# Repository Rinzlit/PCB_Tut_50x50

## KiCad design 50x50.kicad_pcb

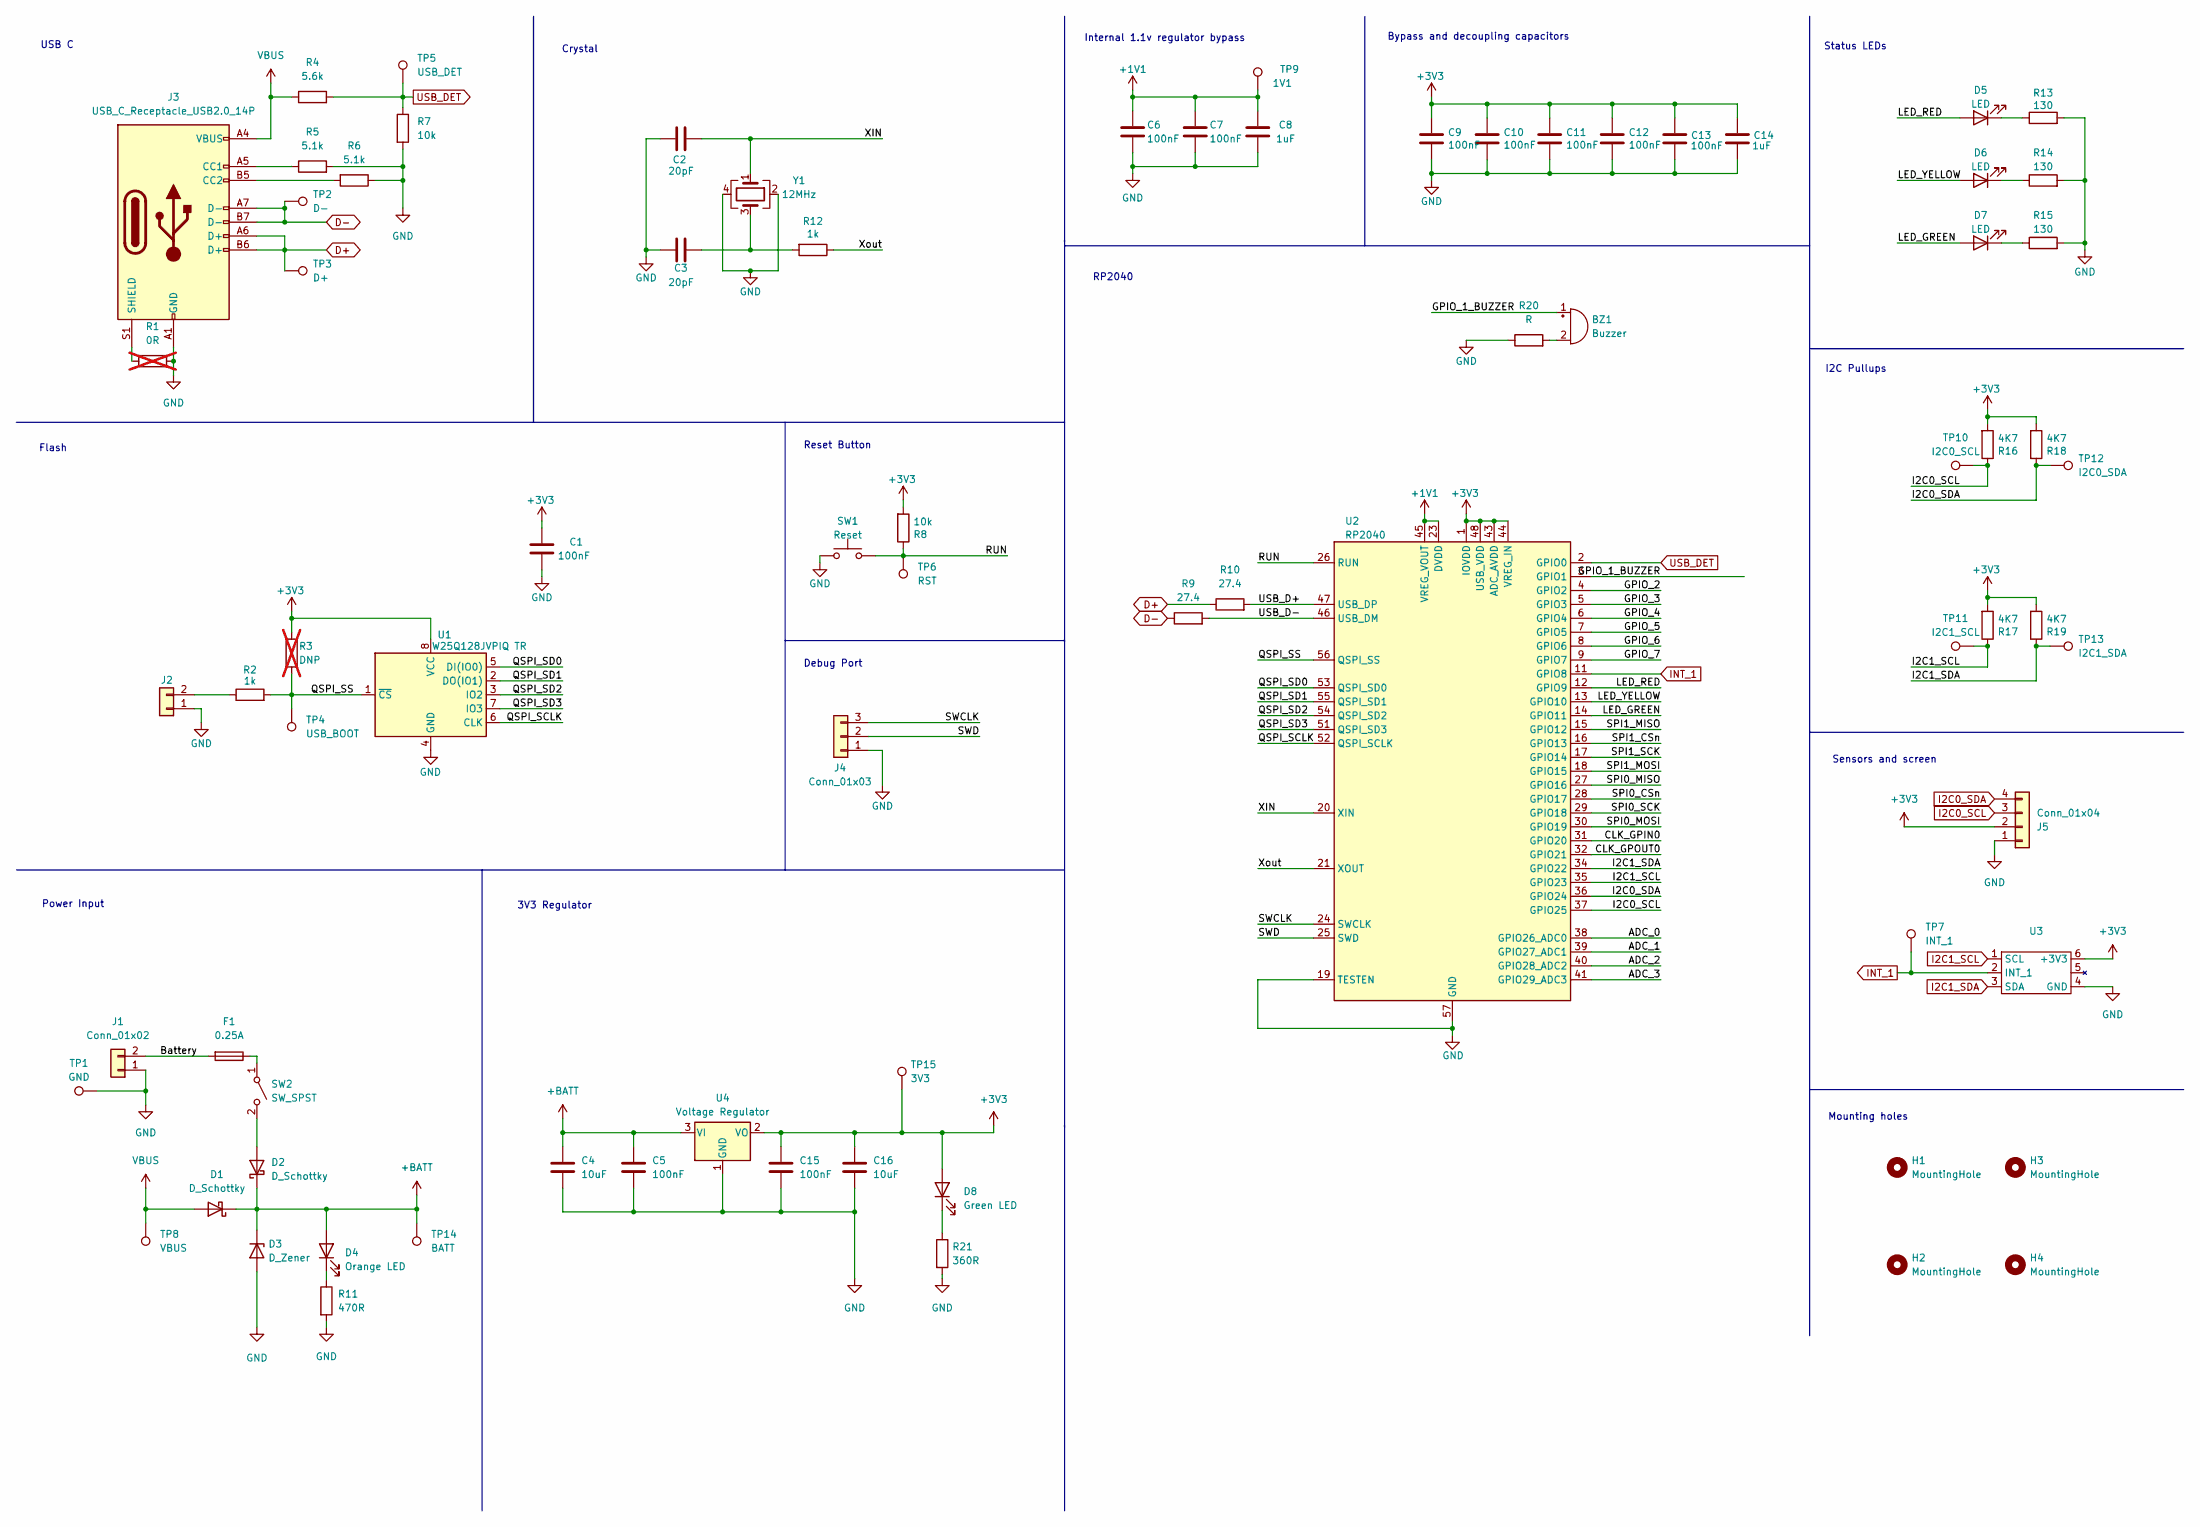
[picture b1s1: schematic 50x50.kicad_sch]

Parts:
BZ1: Buzzer; Buzzer_12x9.5RM7.6
C1, C5, C6, C7, C9, C10, C11, C12, C13, C15: 100nF; C_0805_2012Metric_Pad1.18x1.45mm_HandSolder; MPN CL21B104KCFNNNE; LCSC Part Number C28233
C2, C3: 20pF; C_0805_2012Metric_Pad1.18x1.45mm_HandSolder; MPN 0603N270J500CT; LCSC Part Number C1798
C4, C16: 10uF; C_0805_2012Metric_Pad1.18x1.45mm_HandSolder; MPN CL21C200JBANNNC; LCSC Part Number C15850
C8, C14: 1uF; C_0805_2012Metric_Pad1.18x1.45mm_HandSolder; MPN CL21B105KBFNNNE; LCSC Part Number C28323
D1, D2: D_Schottky; D_SMA; MPN SS34; LCSC Part Number C2909963
D3: D_Zener; D_SOD-123; MPN BZT52C12-TP; LCSC Part Number C668891
D4: Orange LED; LED_0603_1608Metric; MPN ORH-R36A; LCSC Part Number C205445
D5: LED; LED_0402_1005Metric_Pad0.77x0.64mm_HandSolder; MPN 16-213UYC/S530-A2/TR8; LCSC Part Number C136118
D6: LED; LED_0402_1005Metric_Pad0.77x0.64mm_HandSolder; MPN 16-213SYGC/S530-E3/TR8; LCSC Part Number C264408
D7: LED; LED_0402_1005Metric_Pad0.77x0.64mm_HandSolder; MPN 16-213SURC/S530-A4/TR8; LCSC Part Number C74339
D8: Green LED; LED_0603_1608Metric; MPN NCD0603C1; LCSC Part Number C84264
F1: 0.25A; Fuse_0603_1608Metric; MPN 0467.250NRHF; LCSC Part Number C151137
H1, H2, H3, H4: MountingHole; MountingHole_3.2mm_M3
J1: Conn_01x02; JST_XH_B2B-XH-A_1x02_P2.50mm_Vertical; MPN B2B-XH-A(LF)(SN); LCSC Part Number C158012
J2: Conn_01x02; PinHeader_1x02_P2.54mm_Vertical; MPN 2.54-1*2P; LCSC Part Number C49661
J3: USB_C_Receptacle_USB2.0_14P; USB_C_Receptacle_GCT_USB4105-xx-A_16P_TopMnt_Horizontal; MPN GT-USB-7010ASV; LCSC Part Number C2988369
J4: Conn_01x03; PinSocket_1x03_P2.54mm_Vertical; MPN 2.54-1*3P; LCSC Part Number C146243
J5: Conn_01x04; PinSocket_1x04_P2.54mm_Vertical; MPN 2.54-1*4; LCSC Part Number C5116483
R1: 0R; R_0805_2012Metric_Pad1.20x1.40mm_HandSolder; MPN 0805W8F0000T5E; LCSC Part Number C17477; not fitted
R2, R12: 1k; R_0805_2012Metric_Pad1.20x1.40mm_HandSolder; MPN 0805W8F1001T5E; LCSC Part Number C17513
R3: DNP; R_0805_2012Metric_Pad1.20x1.40mm_HandSolder; not fitted
R4: 5.6k; R_0805_2012Metric_Pad1.20x1.40mm_HandSolder; MPN 0805W8F5601T5E; LCSC Part Number C4382
R5, R6: 5.1k; R_0805_2012Metric_Pad1.20x1.40mm_HandSolder; MPN 0805W8F5101T5E; LCSC Part Number C27834
R7, R8: 10k; R_0805_2012Metric_Pad1.20x1.40mm_HandSolder; MPN 0805W8F1002T5E; LCSC Part Number C17414
R9, R10: 27.4; R_0805_2012Metric_Pad1.20x1.40mm_HandSolder; MPN 0805W8F274JT5E; LCSC Part Number C17588
R11: 470R; R_0805_2012Metric_Pad1.20x1.40mm_HandSolder; MPN RC0805FR-07470RL; LCSC Part Number C114564
R13, R14, R15: 130; R_0805_2012Metric_Pad1.20x1.40mm_HandSolder; MPN RC0805JR-07130RL; LCSC Part Number C137474
R16, R17, R18, R19: 4K7; R_0805_2012Metric_Pad1.20x1.40mm_HandSolder; MPN RC0805FR-074K7L; LCSC Part Number C60816
R20: R; R_0805_2012Metric_Pad1.20x1.40mm_HandSolder
R21: 360R; R_0805_2012Metric_Pad1.20x1.40mm_HandSolder; MPN RC0805JR-07360RL; LCSC Part Number C137444
SW1: Reset; SW_SPST_PTS645; MPN KH-6X6X5H-STM; LCSC Part Number C2837531
SW2: SW_SPST; JST_XH_B2B-XH-A_1x02_P2.50mm_Vertical; MPN B2B-XH-A(LF)(SN); LCSC Part Number C158012
TP1: GND; TestPoint_Pad_1.0x1.0mm
TP2: D-; TestPoint_Pad_1.0x1.0mm
TP3: D+; TestPoint_Pad_1.0x1.0mm
TP4: USB_BOOT; TestPoint_Pad_1.0x1.0mm
TP5: USB_DET; TestPoint_Pad_1.0x1.0mm
TP6: RST; TestPoint_Pad_1.0x1.0mm
TP7: INT_1; TestPoint_Pad_1.0x1.0mm
TP8: VBUS; TestPoint_Pad_1.0x1.0mm
TP9: 1V1; TestPoint_Pad_1.0x1.0mm
TP10: I2C0_SCL; TestPoint_Pad_1.0x1.0mm
TP11: I2C1_SCL; TestPoint_Pad_1.0x1.0mm
TP12: I2C0_SDA; TestPoint_Pad_1.0x1.0mm
TP13: I2C1_SDA; TestPoint_Pad_1.0x1.0mm
TP14: BATT; TestPoint_Pad_1.0x1.0mm
TP15: 3V3; TestPoint_Pad_1.0x1.0mm
U1: W25Q128JVPIQ TR; SOIC-8_5.23x5.23mm_P1.27mm; MPN W25Q128JVSIQ; LCSC Part Number C97521
U2: RP2040; QFN-56-1EP_7x7mm_P0.4mm_EP3.2x3.2mm; MPN RP2040; LCSC Part Number C2040
U3: UCA_Sense
U4: Voltage Regulator; SOT-223; MPN AMS1117-3.3; LCSC Part Number C6186
Y1: 12MHz; Crystal_SMD_3225-4Pin_3.2x2.5mm_HandSoldering; MPN X322512MMB4SI; LCSC Part Number C50430

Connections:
+1V1: C6.1, C7.1, C8.2, TP9.1, U2.23 (DVDD), U2.45 (VREG_VOUT), U2.50 (DVDD)
+3V3: C1.2, C9.1, C10.1, C11.1, C12.1, C13.2, C14.2, C15.1, C16.1, D8.2 (A), J5.2, R3.1, R8.2, R16.2, R17.2, R18.2, R19.2, TP15.1, U1.8 (VCC), U2.1 (IOVDD), U2.10 (IOVDD), U2.22 (IOVDD), U2.33 (IOVDD), U2.42 (IOVDD), U2.43 (ADC_AVDD), U2.44 (VREG_IN), U2.48 (USB_VDD), U2.49 (IOVDD), U3.6 (+3V3), U4.2 (VO)
+BATT: C4.1, C5.1, D1.1 (K), D2.1 (K), D3.1 (K), D4.2 (A), TP14.1, U4.3 (VI)
/ADC_0: U2.38 (GPIO26_ADC0)
/ADC_1: U2.39 (GPIO27_ADC1)
/ADC_2: U2.40 (GPIO28_ADC2)
/ADC_3: U2.41 (GPIO29_ADC3)
/Battery: F1.2, J1.2
/CLK_GPIN0: U2.31 (GPIO20)
/CLK_GPOUT0: U2.32 (GPIO21)
/GPIO_1_BUZZER: BZ1.1 (+), U2.3 (GPIO1)
/GPIO_2: U2.4 (GPIO2)
/GPIO_3: U2.5 (GPIO3)
/GPIO_4: U2.6 (GPIO4)
/GPIO_5: U2.7 (GPIO5)
/GPIO_6: U2.8 (GPIO6)
/GPIO_7: U2.9 (GPIO7)
/LED_GREEN: D7.2 (A), U2.14 (GPIO11)
/LED_RED: D5.2 (A), U2.12 (GPIO9)
/LED_YELLOW: D6.2 (A), U2.13 (GPIO10)
/QSPI_SCLK: U1.6 (CLK), U2.52 (QSPI_SCLK)
/QSPI_SD0: U1.5 (DI(IO0)), U2.53 (QSPI_SD0)
/QSPI_SD1: U1.2 (DO(IO1)), U2.55 (QSPI_SD1)
/QSPI_SD2: U1.3 (IO2), U2.54 (QSPI_SD2)
/QSPI_SD3: U1.7 (IO3), U2.51 (QSPI_SD3)
/QSPI_SS: R2.2, R3.2, TP4.1, U1.1 (~CS), U2.56 (QSPI_SS)
/RUN: R8.1, SW1.2, TP6.1, U2.26 (RUN)
/SPI0_CSn: U2.28 (GPIO17)
/SPI0_MISO: U2.27 (GPIO16)
/SPI0_MOSI: U2.30 (GPIO19)
/SPI0_SCK: U2.29 (GPIO18)
/SPI1_CSn: U2.16 (GPIO13)
/SPI1_MISO: U2.15 (GPIO12)
/SPI1_MOSI: U2.18 (GPIO15)
/SPI1_SCK: U2.17 (GPIO14)
/SWCLK: J4.3, U2.24 (SWCLK)
/SWD: J4.2, U2.25 (SWD)
/USB_D+: R10.2, U2.47 (USB_DP)
/USB_D-: R9.2, U2.46 (USB_DM)
/XIN: C2.1, U2.20 (XIN), Y1.1
/Xout: R12.1, U2.21 (XOUT)
D+: J3.A6 (D+), J3.B6 (D+), R10.1, TP3.1
D-: J3.A7 (D-), J3.B7 (D-), R9.1, TP2.1
GND: C1.1, C2.2, C3.2, C4.2, C5.2, C6.2, C7.2, C8.1, C9.2, C10.2, C11.2, C12.2, C13.1, C14.1, C15.2, C16.2, D3.2 (A), J1.1, J2.1, J3.A1 (GND), J3.A12 (GND), J3.B1 (GND), J3.B12 (GND), J4.1, J5.1, R1.2, R5.2, R6.1, R7.2, R11.2, R13.2, R14.2, R15.2, R20.1, R21.2, SW1.1, TP1.1, U1.4 (GND), U2.19 (TESTEN), U2.57 (GND), U3.4 (GND), U4.1 (GND), Y1.2, Y1.4
I2C0_SCL: J5.3, R16.1, TP10.1, U2.37 (GPIO25)
I2C0_SDA: J5.4, R18.1, TP12.1, U2.36 (GPIO24)
I2C1_SCL: R17.1, TP11.1, U2.35 (GPIO23), U3.1 (SCL)
I2C1_SDA: R19.1, TP13.1, U2.34 (GPIO22), U3.3 (SDA)
INT_1: TP7.1, U2.11 (GPIO8), U3.2 (INT_1)
unnamed: BZ1.2 (-), R20.2
unnamed: C3.1, R12.2, Y1.3
unnamed: D2.2 (A), SW2.2 (B)
unnamed: D4.1 (K), R11.1
unnamed: D5.1 (K), R13.1
unnamed: D6.1 (K), R14.1
unnamed: D7.1 (K), R15.1
unnamed: D8.1 (K), R21.1
unnamed: J2.2, R2.1
unnamed: J3.A5 (CC1), R5.1
unnamed: J3.B5 (CC2), R6.2
unnamed: J3.S1 (SHIELD), R1.1
unnamed: F1.1, SW2.1 (A)
USB_DET: R4.2, R7.1, TP5.1, U2.2 (GPIO0)
VBUS: D1.2 (A), J3.A4 (VBUS), J3.A9 (VBUS), J3.B4 (VBUS), J3.B9 (VBUS), R4.1, TP8.1

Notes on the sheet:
Internal 1.1v regulator bypass
Power Input
RP2040
Bypass and decoupling capacitors
Crystal
Status LEDs
Reset Button
3V3 Regulator
Flash
USB C
Mounting holes
I2C Pullups
Debug Port
Sensors and screen

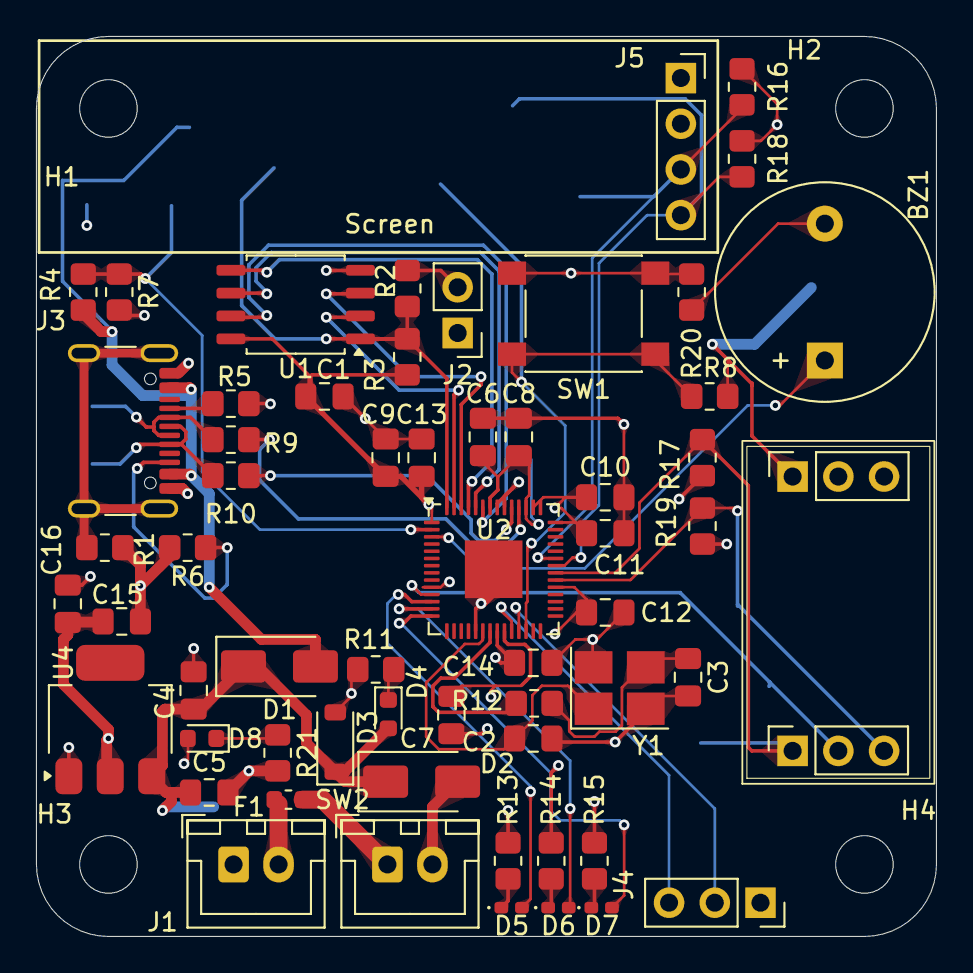
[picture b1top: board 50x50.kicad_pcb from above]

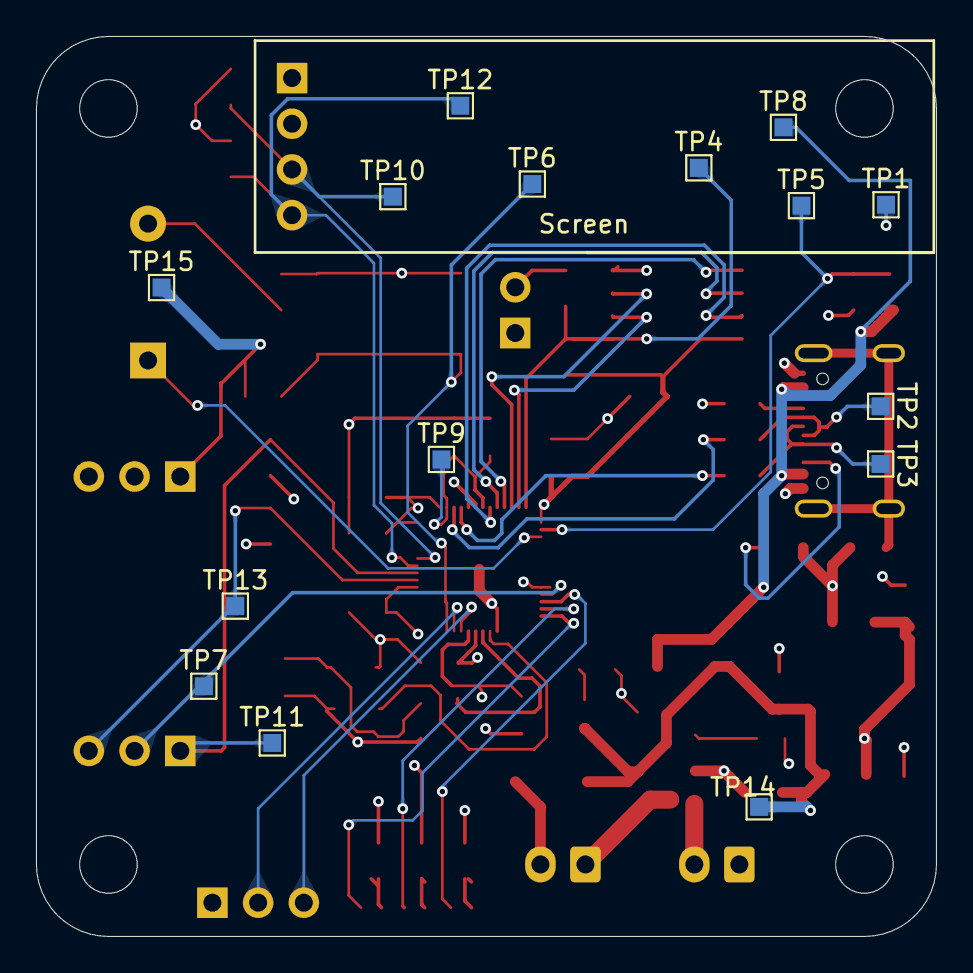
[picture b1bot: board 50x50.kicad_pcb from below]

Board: 4 copper layers, 50.0 x 50.0 mm, 78 parts (15 on the bottom side), 44 nets.

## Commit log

2024-07-03 original
2024-07-03 feat: removed via's from pads
2024-07-03 fix: no 90 degree angle
2024-07-06 fix: moved all vias from under pads
